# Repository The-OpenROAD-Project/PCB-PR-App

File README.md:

# PCB-PR-App

Top-level app for PCB P&R flow

### Prerequisites

- GCC >=4.8
- G++ >= 4.8
```
export CXX=g++
```
- SWIG >= 2.0
```
sudo apt-get update
sudo apt-get install swig
```
- Boost >= 1.6
```
sudo apt-get update
sudo apt-get install libboost-all-dev
```
- CMake >= 3.1
```
sudo apt-get update
sudo apt-get install cmake
```
- Current support for kicad_pcb format derived from KiCad v5.1.2

### Installing

Clone
```
git clone --recurse-submodules https://github.com/The-OpenROAD-Project/PCB-PR-App.git
```

Run the build script:
```
cd PCB-PR-App
source build.sh
```

The layout app is now available:
```
python3 run_layout.py --help
```

Have fun!

## Running the tests

## Current issues

- Tested on CentOS 6
- Tested on Ubuntu 18.04 (Ubuntu 16.04 doesn't come with Python 3)
- Linking shared object files after swig compilation currently fails on OSX. Docker is a good workaround on OSX.

## License
  * BSD-3-clause License [[Link]](LICENSE)

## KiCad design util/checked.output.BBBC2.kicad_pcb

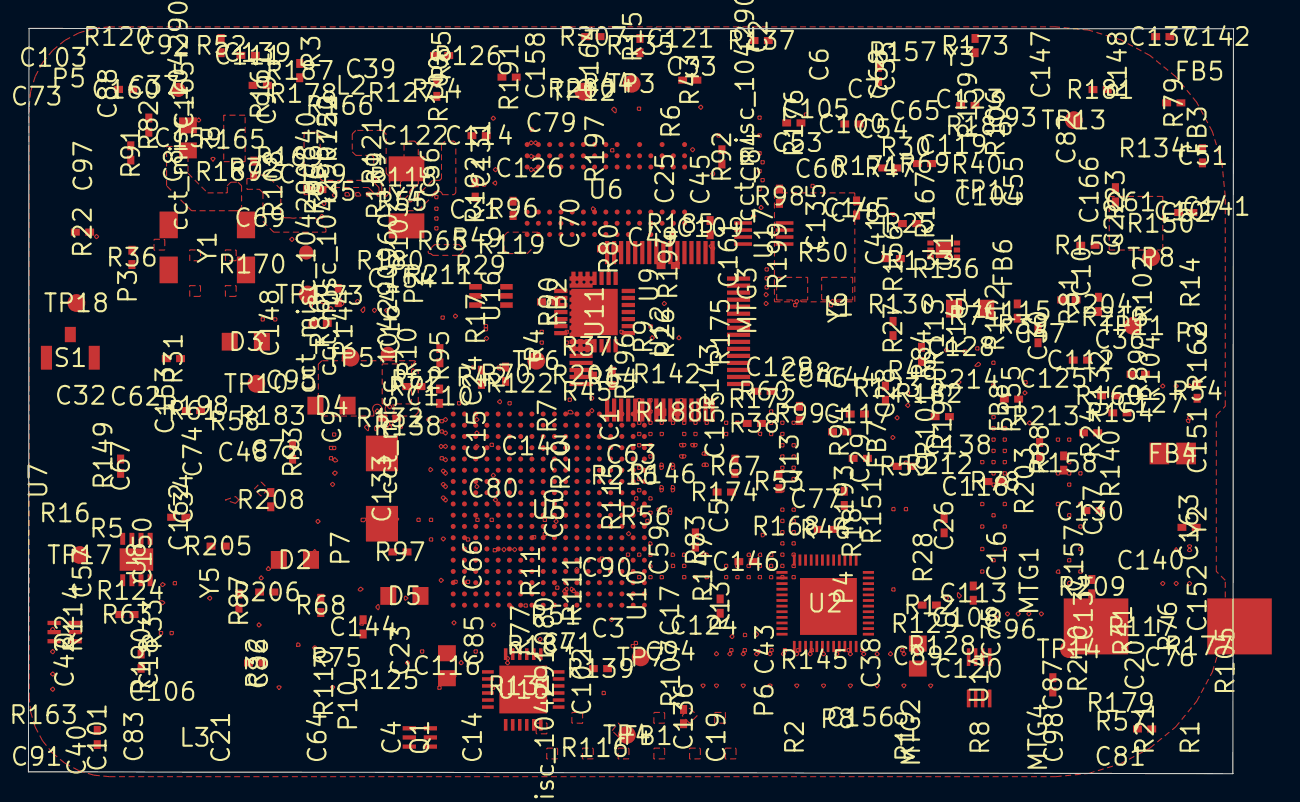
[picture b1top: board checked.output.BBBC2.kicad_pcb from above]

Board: 4 copper layers, 85.7 x 53.0 mm, 452 parts (0 on the bottom side), 309 nets, no tracks yet.

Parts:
C1: C1
C2: C2
C3: C3
C4: C4
C5: C5
C6: C6
C7: C7
C8: C8
C9: C9
C10: C10
C14: C14
C15: C15
C16: C16
C17: C17
C18: C18
C19: C19
C20: C20
C21: C21
C22: C22
C23: C23
C24: C24
C25: C25
C26: C26
C27: C27
C28: C28
C29: C29
C30: C30
C31: C31
C32: C32
C33: C33
C34: C34
C35: C35
C36: C36
C37: C37
C38: C38
C39: C39
C40: C40
C41: C41
C42: C42
C43: C43
C44: C44
C45: C45
C46: C46
C47: C47
C48: C48
C49: C49
C50: C50
C51: C51
C52: C52
C53: C53
C54: C54
C55: C55
C56: C56
C57: C57
C58: C58
C59: C59
C60: C60
C61: C61
C62: C62
C63: C63
C64: C64
C65: C65
C66: C66
C67: C67
C68: C68
C69: C69
C70: C70
C71: C71
C72: C72
C73: C73
C74: C74
C75: C75
C76: C76
C77: C77
C78: C78
C79: C79
C80: C80
C81: C81
C82: C82
C83: C83
C84: C84
C85: C85
C86: C86
C87: C87
C88: C88
C89: C89
C90: C90
C91: C91
C92: C92
C93: C93
C94: C94
C95: C95
C96: C96
C97: C97
C98: C98
C99: C99
C100: C100
C101: C101
C102: C102
C103: C103
C104: C104
C105: C105
C106: C106
C107: C107
C108: C108
C109: C109
C110: C110
C111: C111
C112: C112
C113: C113
C114: C114
C115: C115
C116: C116
C117: C117
C118: C118
C119: C119
C120: C120
C121: C121
C122: C122
C123: C123
C124: C124
C125: C125
C126: C126
C127: C127
C128: C128
C129: C129
C130: C130
C131: C131
C132: C132
C133: C133
C134: C134
C135: C135
C136: C136
C137: C137
C138: C138
C139: C139
C140: C140
C141: C141
C142: C142
C143: C143
C144: C144
C145: C145
C146: C146
C147: C147
C148: C148
C149: C149
C150: C150
C151: C151
C152: C152
C153: C153
C154: C154
C155: C155
C156: C156
C157: C157
C158: C158
C159: C159
C160: C160
C161: C161
C162: C162
C163: C163
C164: C164
C165: C165
C166: C166
D1: D1
D2: D2
D3: D3
D4: D4
D5: D5
FB1: FB1
FB2: FB2
FB3: FB3
FB4: FB4
FB5: FB5
FB6: FB6
FB7: FB7
FB8: FB8
L1: L1
L2: L2
L3: L3
MTG1: MTG1
MTG2: MTG2
MTG3: MTG3
MTG4: MTG4
P2: P2
P3: P3
P4: P4
P5: P5
P6: P6
P7: P7
P8: P8
P9: P9
P10: P10
Q1: Q1
Q2: Q2
R1: R1
R2: R2
R3: R3
R4: R4
R5: R5
R6: R6
R7: R7
R8: R8
R9: R9
R10: R10
R11: R11
R12: R12
R13: R13
R14: R14
R15: R15
R16: R16
R17: R17
R18: R18
R19: R19
R20: R20
R21: R21
R22: R22
R23: R23
R24: R24
R25: R25
R26: R26
R27: R27
R28: R28
R29: R29
R30: R30
R31: R31
R32: R32
R33: R33
R34: R34
R35: R35
R36: R36
R37: R37
R38: R38
R39: R39
R40: R40
R41: R41
R42: R42
R43: R43
R44: R44
R45: R45
R46: R46
R47: R47
R48: R48
R49: R49
R50: R50
R51: R51
R52: R52
R53: R53
R54: R54
R55: R55
R56: R56
R57: R57
R58: R58
R59: R59
R60: R60
R61: R61
R62: R62
R63: R63
R64: R64
R65: R65
R66: R66
R67: R67
R68: R68
R69: R69
R70: R70
R71: R71
R72: R72
R73: R73
R74: R74
R75: R75
R76: R76
R77: R77
R78: R78
R79: R79
R80: R80
R81: R81
R82: R82
R83: R83
R84: R84
R85: R85
R86: R86
R87: R87
R88: R88
R89: R89
R90: R90
R91: R91
R92: R92
R93: R93
R94: R94
R95: R95
R96: R96
R97: R97
R98: R98
R99: R99
R100: R100
R101: R101
R102: R102
R103: R103
R104: R104
R105: R105
R106: R106
R107: R107
R108: R108
R109: R109
R110: R110
R111: R111
R112: R112
R113: R113
R114: R114
R115: R115
R116: R116
R117: R117
R118: R118
R119: R119
R120: R120
R121: R121
R122: R122
R123: R123
R124: R124
R125: R125
R126: R126
R127: R127
R128: R128
R129: R129
R130: R130
R131: R131
R132: R132
R133: R133
R134: R134
R135: R135
R136: R136
R137: R137
R138: R138
R139: R139
R140: R140
R141: R141
R142: R142
R143: R143
R144: R144
R145: R145
R146: R146
R147: R147
R148: R148
R149: R149
R150: R150
R151: R151
R152: R152
R153: R153
R154: R154
R155: R155
R156: R156
R157: R157
R158: R158
R159: R159
R160: R160
R161: R161
R162: R162
R163: R163
R164: R164
R165: R165
R166: R166
R167: R167
R168: R168
R169: R169
R170: R170
R171: R171
R172: R172
R173: R173
R174: R174
R175: R175
R176: R176
R177: R177
R178: R178
R179: R179
R180: R180
R181: R181
R182: R182
R183: R183
R184: R184
R185: R185
R186: R186
R187: R187
R188: R188
R189: R189
R190: R190
R191: R191
R192: R192
R193: R193
R194: R194
R195: R195
R196: R196
R197: R197
R198: R198
R199: R199
R200: R200
R201: R201
R203: R203
R204: R204
R205: R205
R206: R206
R207: R207
R208: R208
R209: R209
R210: R210
R211: R211
R212: R212
R213: R213
R214: R214
R215: R215
R216: R216
S1: S1
TP1: TP1
TP3: TP3
TP4: TP4
TP5: TP5
TP6: TP6
TP7: TP7
TP8: TP8
TP10: TP10
TP11: TP11
TP12: TP12
TP13: TP13
TP14: TP14
TP15: TP15
TP17: TP17
TP18: TP18
U1: U1
U2: U2
U5: U5
U6: U6
U7: U7
U8: U8
U9: U9
U10: U10
U11: U11
U12: U12
U13: U13
U14: U14
U15: U15
U16: U16
U17: U17
Y1: Y1
Y2: Y2
Y3: Y3
Y4: Y4
Y5: Y5
Y6: Y6
cct_misc_104290480: cct_misc_104290480
cct_misc_104290600: cct_misc_104290600
cct_misc_104290720: cct_misc_104290720
cct_misc_104290840: cct_misc_104290840
cct_misc_104290960: cct_misc_104290960
cct_misc_104291080: cct_misc_104291080

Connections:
3V3EXP_FB: C166.1, R150.1, R189.1, U8.3
AGND: R15.1, U2.41
AIN7: R8.1, R9.2, U5.C9
BAT: C3.2, U2.4, U2.5
BL_OUT: C7.1, U2.38
CAP_VBB_MPU: C85.1, U5.C10
CAP_VDD_SRAM_CORE: C83.1, U5.D9
CAP_VDD_SRAM_MPU: C84.1, U5.D11
CD/EMU4: R185.1, R197.2, U5.C15
CLKOUT2: R184.2, U5.D14
COL/CRS_DV/MODE2: R207.2, U15.15
CRFILT: C146.1, U11.9
CRS_DV/MODE2: R122.1, R127.1, R139.2, U15.14
DC_IN: C1.1, U1.4, U1.5, U2.10
DDR_A0: R29.1, U6.M8
DDR_A1: R25.1, U6.M3
DDR_A2: R30.1, U6.M7
DDR_A3: R26.1, U6.N2
DDR_A4: R31.1, U6.N8
DDR_A5: R32.1, U6.N3
DDR_A6: R33.1, U6.N7
DDR_A7: R34.1, U6.P2
DDR_A8: R35.1, U6.P8
DDR_A9: R36.1, U6.P3
DDR_A10: R37.1, U6.M2
DDR_A11: R38.1, U6.P7
DDR_A12: R39.1, U6.R2
DDR_A13: R40.1, R120.1
DDR_A13R: R120.2, U6.R8
DDR_BA0: R41.1, U6.L2
DDR_BA1: R42.1, U6.L3
DDR_BA2: R43.1, U6.L1
DDR_CASN: R64.1, U6.L7
DDR_CKE: R62.1, U6.K2
DDR_CLK: R60.1, U6.J8
DDR_CLKN: R61.1, U6.K8
DDR_CSN: R63.1, U6.L8
DDR_D0: R44.1, U6.G8
DDR_D1: R45.1, U6.G2
DDR_D2: R46.1, U6.H7
DDR_D3: R47.1, U6.H3
DDR_D4: R48.1, U6.H1
DDR_D5: R49.1, U6.H9
DDR_D6: R50.1, U6.F1
DDR_D7: R51.1, U6.F9
DDR_D8: R52.1, U6.C8
DDR_D9: R53.1, U6.C2
DDR_D10: R54.1, U6.D7
DDR_D11: R55.1, U6.D3
DDR_D12: R56.1, U6.D1
DDR_D13: R57.1, U6.D9
DDR_D14: R58.1, U6.B1
DDR_D15: R59.1, U6.B9
DDR_DQM0: R67.1, U6.F3
DDR_DQM1: R70.1, U6.B3
DDR_DQS0: R68.1, U6.F7
DDR_DQS1: R71.1, U6.B7
DDR_DQSN0: R69.1, U6.E8
DDR_DQSN1: R72.1, U6.A8
DDR_ODT: R73.1, U6.K9
DDR_RASN: R65.1, U6.K7
DDR_RESETN: TP3.1, U5.G2
DDR_VREF: C118.1, R74.2, R75.1, U5.J4, U6.J2
DDR_VTP: R76.1, U5.J3
DDR_WEN: R66.1, U6.K3
DGND: C1.2, C2.2, C3.1, C4.1, C5.1, C6.2, C7.2, C8.1, C9.1, C10.1, C14.1, C15.1, C16.2, C17.1, C18.1, C19.1, C20.2, C21.2, C22.2, C25.2, C31.1, C32.1, C33.2, C34.2, C35.2, C36.2, C37.2, C38.2, C39.2, C40.2, C41.2, C42.2, C43.1, C44.1, C45.2, C46.2, C47.2, C48.2, C49.2, C50.1, C51.2, C52.1, C53.2, C54.2, C55.2, C56.2, C57.2, C58.1, C59.1, C60.2, C61.2, C62.1, C63.1, C64.1, C65.1, C66.1, C67.1, C68.1, C69.2, C70.1, C71.1, C72.2, C73.2, C74.2, C75.2, C76.2, C77.2, C78.2, C79.2, C80.2, C81.2, C82.2, C83.2, C84.2, C85.2, C86.2, C88.2, C89.1, C90.2, C91.2, C92.2, C93.2, C94.2, C95.2, C96.2, C97.2, C98.2, C100.2, C101.2, C102.2, C103.2, C104.2, C105.2, C106.2, C107.2, C108.2, C109.2, C110.2, C111.2, C112.2, C113.2, C114.2, C115.2, C116.2, C117.2, C118.2, C119.2, C120.2, C121.2, C122.2, C123.2, C124.2, C125.2, C126.2, C127.2, C128.2, C129.2, C130.2, C131.2, C132.2, C133.2, C134.2, C135.1, C136.2, C137.1, C138.2, C139.2, C140.2, C141.2, C142.2, C143.2, C144.1, C145.2, C146.2, C147.2, C148.2, C149.1, C150.2, C151.2, C152.2, C153.1, C154.2, C155.1, C156.2, C157.1, C158.2, C159.2, C160.2, C161.2, C162.1, C163.1, C164.1, C165.1, D1.1, FB3.2, P3.5, P4.6, P4.9, P7.8, P7.10, P7.12, P7.16, P7.20, Q1.1, Q1.4, Q2.1, Q2.4, R1.1, R5.2, R9.1, R15.2, R16.1, R18.2, R20.2, R75.2, R76.2, R79.1, R100.2, R101.2, R102.2, R103.2, R104.2, R105.2, R106.2, R107.2, R108.2, R109.2, R110.2, R111.2, R112.2, R113.2, R114.2, R115.2, R116.2, R117.2, R118.2, R119.2, R125.2, R127.2, R128.1, R138.1, R145.2, R146.2, R147.2, R151.2, R157.2, R158.2, R159.2, R161.1, R167.1, R177.2, R186.2, R189.2, R198.2, R212.2, R214.2, R216.2, S1.1, U1.2, U1.6, U2.30, U2.49, U5.A1, U5.A18, U5.F8, U5.G8, U5.G9, U5.G11, U5.G12, U5.H6, U5.H7, U5.H8, U5.H9, U5.H10, U5.H12, U5.J6, U5.J7, U5.J8, U5.J9, U5.J10, U5.J11, U5.K7, U5.K9, U5.K10, U5.K11, U5.L10, U5.L11, U5.L12, U5.L13, U5.M6, U5.M7, U5.M8, U5.M9, U5.M10, U5.M12, U5.M14, U5.N7, U5.N10, U5.N11, U5.N14, U5.V1, U5.V18, U6.A3, U6.A7, U6.B2, U6.B8, U6.D2, U6.D8, U6.E3, U6.E7, U6.F2, U6.F8, U6.H2, U6.H8, U6.J3, U6.J7, U6.N1, U6.P9, U7.1, U8.4, U8.9, U9.9, U10.4, U11.6, U11.29, U12.1, U12.5, U12.10, U12.11, U12.13, U12.15, U12.25, U12.32, U12.35, U12.47, U12.51, U13.2, U14.4, U15.33, U16.2, U17.4
EMU2R: P7.17, R183.2
EMU3R: P7.18, R184.1
EMU4R: P7.19, R185.2
EMU_RSTN: C156.1, P7.15, R182.2
ENZ_KALDO_1P8V: R79.2, U5.B4
FT_DM: U11.28, U12.7
FT_DP: U11.1, U12.8
FT_REF: R167.2, U12.6
FT_RESETN: R175.2, U12.14
FT_SRESET: R162.2, R172.2, R182.1, U14.5
FT_SRESETB: R163.1, U16.6
FT_SRESETN: U14.3, U16.1
FT_VBUS: R181.2, U11.7, U12.59, U14.6
F_ADBUS0: R164.1, U12.16
F_ADBUS1: R165.1, U12.17
F_ADBUS2: R166.1, U12.18
F_ADBUS3: R168.1, U12.19
F_ADBUS4: R169.1, U12.21
F_ADBUS5: R172.1, U12.26
F_ADBUS6: R170.1, U12.23
F_ADBUS7: R171.1, U12.30
F_EECS: R173.2, U12.63, U13.5
F_EEDATA: R188.2, U12.61, U13.3
F_EEDOUT: R187.2, R188.1, U13.1
F_EESK: R174.2, U12.62, U13.4
GNDA_ADC: C28.2, C29.2, C30.2, C87.2, FB3.1, U5.A9, U5.E8
GND_EARTH: P3.6, P3.7, P3.8, P3.9, P4.11, P4.12, P4.13, P4.14, P4.15, P4.16, R138.2, S1.3
GND_OSC0: C26.2, C27.2, C99.2, U5.V11
GND_OSC1: C23.1, C24.1, U5.A5
GPIO2_6: R80.2, R100.1, U5.R1
GPIO2_7: R81.2, R101.1, U5.R2
GPIO2_8: R82.2, R102.1, U5.R3
GPIO2_9: R83.2, R103.1, U5.R4
GPIO2_10: R84.2, R104.1, U5.T1
GPIO2_11: R85.2, R105.1, U5.T2
GPIO2_13: R87.2, R107.1, U5.T4
GPIO_12: R86.2, R106.1, U5.T3
HS_IND: TP8.1, U11.16
HUB_BIAS: R157.1, U11.26
I2C0_SCL: R7.2, U2.28, U5.C16
I2C0_SDA: R4.2, U2.27, U5.C17
JTAG_EMU0: P7.13, R170.2, R176.2, U5.C14
JTAG_EMU1: P7.14, R171.2, R179.2, U5.B14
JTAG_TCK: R164.2, R178.1, R180.1, U5.A12
JTAG_TDI: P7.3, R165.2, U5.B11
JTAG_TDO: P7.7, R166.2, U5.A11
JTAG_TMS: P7.1, R168.2, U5.C11
JTAG_TRSTN: P7.2, R169.2, R186.1, U5.B10
LDO3: R19.1, U2.40
LDO4: R121.1, U2.43
LDO_PGOOD: R141.2, U2.46
LEDAA: D2.2, R96.2, TP10.1
LEDAC: D2.1, Q1.6
LEDBA: D3.2, R97.2, TP11.1
LEDBC: D3.1, Q1.3
LEDCA: D4.2, R98.2, TP12.1
LEDCC: D4.1, Q2.6
LEDDA: D5.2, R99.2, TP13.1
LEDDC: D5.1, Q2.3
MDIO_DATA: R131.2, U5.M17
MMC0_CLKO: P4.5, R192.2, U5.G17
MMC0_CMD: P4.3, R191.2, U5.G18
MMC0_DAT0: P4.7, R193.2, U5.G16
MMC0_DAT1: P4.8, R194.2, U5.G15
MMC0_DAT2: P4.1, R190.2, U5.F18
MMC0_DAT3: P4.2, R195.2, U5.F17
N21069846: R199.2, R200.2, U15.5
NINT/RXCLK/PHYAD1: R215.1, R216.1
NON_REM1: R154.2, R158.1, U11.13
NON_REM2: R155.2, R159.1, TP7.1, U11.19
OSC0_IN: C26.1, R21.1, U5.V10, Y2.3, Y3.3
OSC0_OUT: R24.2, U5.U11
OSC0_OUT1: C27.1, R21.2, R24.1, Y2.1, Y3.1
OSC1_IN: C23.2, U5.A6, Y1.1
OSC1_OUT: R22.2, U5.A4
OSC1_OUT1: C24.2, R22.1, Y1.2
PDDR_A0: R29.2, U5.F3
PDDR_A1: R25.2, U5.H1
PDDR_A2: R30.2, U5.E4
PDDR_A3: R26.2, U5.C3
PDDR_A4: R31.2, U5.C2
PDDR_A5: R32.2, U5.B1
PDDR_A6: R33.2, U5.D5
PDDR_A7: R34.2, U5.E2
PDDR_A8: R35.2, U5.D4
PDDR_A9: R36.2, U5.C1
PDDR_A10: R37.2, U5.F4
PDDR_A11: R38.2, U5.F2
PDDR_A12: R39.2, U5.E3
PDDR_A13: R40.2, U5.H3
PDDR_BA0: R41.2, U5.C4
PDDR_BA1: R42.2, U5.E1
PDDR_BA2: R43.2, U5.B3
PDDR_CASN: R64.2, U5.F1
PDDR_CKE: R62.2, U5.G3
PDDR_CLK: R60.2, U5.D2
PDDR_CLKN: R61.2, U5.D1
PDDR_CSN: R63.2, U5.H2
PDDR_D0: R44.2, U5.M3
PDDR_D1: R45.2, U5.M4
PDDR_D2: R46.2, U5.N1
PDDR_D3: R47.2, U5.N2
PDDR_D4: R48.2, U5.N3
PDDR_D5: R49.2, U5.N4
PDDR_D6: R50.2, U5.P3
PDDR_D7: R51.2, U5.P4
PDDR_D8: R52.2, U5.J1
PDDR_D9: R53.2, U5.K1
PDDR_D10: R54.2, U5.K2
PDDR_D11: R55.2, U5.K3
PDDR_D12: R56.2, U5.K4
PDDR_D13: R57.2, U5.L3
PDDR_D14: R58.2, U5.L4
PDDR_D15: R59.2, U5.M1
PDDR_DQM0: R67.2, U5.M2
PDDR_DQM1: R70.2, U5.J2
PDDR_DQS0: R68.2, U5.P1
PDDR_DQS1: R71.2, U5.L1
PDDR_DQSN0: R69.2, U5.P2
PDDR_DQSN1: R72.2, U5.L2
PDDR_ODT: R73.2, U5.G1
PDDR_RASN: R65.2, U5.G4
PDDR_WEN: R66.2, U5.B2
PHYX: C131.1, R144.2, Y4.2
PHY_VDDCR: C124.1, C125.1, U15.6
PHY_XTAL1: C132.1, R140.2, R199.1, Y4.1
PHY_XTAL2: R140.1, R144.1, U15.4
PLLFILT: C145.1, U11.25
PMIC_INT: R10.2, R28.2, U5.B18
PMIC_INT_PU: R28.1, U14.7
PMIC_INT_SRC: R10.1, R203.2, U2.45, U14.1, U14.2
PMIC_PGOOD: C25.1, R20.1, U2.26, U5.B15
PMIC_POWR_EN: U2.9, U5.C6
PWR_LED: R6.1, U2.1
PWR_LEDR: D1.2, R6.2, TP14.1
P_BYPASS: C5.2, U2.47
P_INT_LDO: C4.2, U2.48
P_MUXIN: R1.2, R2.1, U2.14
P_MUXOUT: R8.2, U2.16
P_WAKEUP: R11.1, U2.13
REFCLKO: R136.2, R209.2, U15.7
RESETN: C136.1, R156.2, U11.17
RMII1_COL: R207.1, U5.H16
RMII1_CRS_DV: R139.1, U5.H17
RMII1_REFCLK: R200.1, R201.2, R209.1
RMII1_RXCLK: R136.1, U5.L18
RMII1_RXD0: R135.1, U5.M16
RMII1_RXD1: R132.1, U5.L15
RMII1_RXD2: R153.1, U5.L16
RMII1_RXD3: R205.1, U5.L17
RMII1_RXDV: R208.1, U5.J17
RMII1_RXERR: R137.1, U5.J15
RMII1_TXCLK: R206.1, U5.K18
RMII1_TXD0: U5.K17, U15.22
RMII1_TXD1: U5.K16, U15.23
RMII1_TXEN: U5.J16, U15.21
RSVD3: R161.2, U11.15
RTCK: P7.9, R178.2
RTC_PORZ: R18.1, R141.1, R143.2, U5.B5
RXD0/MODE0: R124.1, R135.2, R198.1, U15.11
RXD1/MODE1: R5.1, R123.1, R132.2, U15.10
RXD2/RMIISEL: R153.2, R211.1, R212.1
RXD3/PHYAD2: R205.2, R213.1, R214.1
RXDV: R208.2, U15.26
RXER/PHYAD0: R125.1, R126.2, R137.2, U15.13
RXN: C127.1, R130.1, U15.30
RXP: C126.1, R129.1, U15.31
SD_CD: P4.10, R196.1, R197.1
SYS_5V: C133.1, FB4.2, R3.2, R152.1, U2.7, U2.8
SYS_RESETN: R23.2, R27.1, U5.A10, U15.19
SYS_VOLT: C6.1, C8.2, C9.2, C10.2, C17.2, C18.2, C19.2, R2.2, R3.1, U2.2, U2.21, U2.22, U2.32, U2.39, U2.42, U8.8
SYS_WARMRESETN: C101.1, R27.2, R163.2, S1.2
TCK: P7.11, R180.2
TCT_RCT: C130.1, R142.1
TDIS: P7.4, R177.1
TESTOUT: TP6.1, U5.A3
TXCLK: R206.2, U15.20
TXN: C129.1, R134.1, U15.28
TXP: C128.1, R133.1, U15.29
U5_H18: R201.1, U5.H18
UART0_CTS: U5.E17, U12.40
UART0_RTS: U5.E18, U12.41
UART0_RX: U5.E16, U12.39
UART0_TX: U5.E15, U12.38
UART3_CTSN: R90.2, R110.1, U5.U3
UART3_RTSN: R91.2, R111.1, U5.U4
UART4_CTSN: R92.2, R112.1, U5.V2
UART4_RTSN: R93.2, R113.1, U5.V3
UART5_CTSN: R94.2, R114.1, U5.V4
UART5_RTSN: R95.2, R115.1, U5.T5
UART5_RXD: R89.2, R109.1, U5.U2
UART5_TXD: R88.2, R108.1, U5.U1
USB0_DM: U5.N18, U11.2
USB0_DP: U5.N17, U11.3
USB0_ID: TP4.1, U5.P16
USB0_VBUS: R152.2, U5.P15, U16.4
USB0_VBUS_PWR: U11.11, U16.3
USB1_DM: U5.R18, U10.2
USB1_DP: U5.R17, U10.1
USB1_DRVVBUS: R147.1, U5.F15
USB1_ID: R146.1, U5.P17
USB1_OC: R148.2, U5.T16
USB1_VBUS: C134.1, U5.T18, U10.6
USBDM_DN: P3.2, U11.21
USBDP_UP: P3.3, U11.22
USB_DC: C2.1, P3.1, R149.1, U2.12
USR0: Q1.2, R116.1, U5.V15
USR1: Q1.5, R117.1, U5.U15
USR2: Q2.2, R118.1, U5.T15
USR3: Q2.5, R119.1, U5.V16
VBUS_DET: R149.2, R151.1, U11.18
VDCDC1: R12.1, U2.19
VDCDC2: R204.1, U2.24
VDCDC3: R13.1, U2.29
VDDS_DDR: C89.2, C90.1, C91.1, C92.1, C93.1, C94.1, C95.1, C96.1, C103.1, C104.1, C105.1, C106.1, C107.1, C108.1, C109.1, C110.1, C111.1, C112.1, C113.1, C114.1, C115.1, C116.1, C117.1, R14.2, R74.1, TP18.1, U5.E5, U5.F5, U5.G5, U5.H5, U5.J5, U5.K5, U5.L5, U6.A1, U6.A9, U6.C1, U6.C3, U6.C7, U6.C9, U6.E1, U6.E9, U6.G1, U6.G3, U6.G7, U6.G9, U6.J1, U6.J9, U6.M9, U6.R1
VDD_1V8: C16.1, C72.1, C74.1, C75.1, C76.1, C77.1, C78.1, C79.1, C80.1, C82.1, C86.1, FB1.1, FB2.2, R12.2, R14.1, TP15.1, U5.D10, U5.E6, U5.E7, U5.E9, U5.E14, U5.F9, U5.K13, U5.N6, U5.N16, U5.P9, U5.P14, U5.R16
VDD_1V8FT: C152.1, C162.2, C163.2, C164.2, U12.12, U12.37, U12.49, U12.64
VDD_3V3A: C42.1, C43.2, C51.1, C52.2, C56.1, C57.1, C58.2, C59.2, C60.1, C61.1, C62.2, C63.2, C64.2, C65.2, C66.2, C67.2, C68.2, C69.1, C70.2, C71.2, C81.1, C159.1, C160.1, C165.2, P4.4, R4.1, R7.1, R19.2, R23.1, R80.1, R81.1, R82.1, R83.1, R84.1, R85.1, R86.1, R87.1, R88.1, R89.1, R90.1, R91.1, R92.1, R93.1, R94.1, R95.1, R190.1, R191.1, R192.1, R193.1, R194.1, R195.1, U2.18, U5.E10, U5.E11, U5.E12, U5.E13, U5.F14, U5.G14, U5.H14, U5.J14, U5.K14, U5.L14, U5.N5, U5.N15, U5.P5, U5.P6, U5.P7, U5.P8, U5.P10, U5.P11, U5.P12, U5.P13, U5.R15, U8.5
VDD_3V3B: C102.1, C122.1, C123.1, C135.2, C138.1, C139.1, C140.1, C141.1, C142.1, C143.1, C147.1, C148.1, C149.2, C150.1, C151.1, C154.1, C157.2, FB5.1, FB6.1, FB7.1, FB8.1, P7.5, R121.2, R122.2, R123.2, R124.2, R126.1, R131.1, R148.1, R154.1, R155.1, R156.1, R162.1, R173.1, R174.1, R175.1, R176.1, R179.1, R181.1, R187.1, R196.2, R203.1, R210.1, R211.2, R213.2, R215.2, U11.4, U11.10, U11.14, U11.20, U11.27, U12.20, U12.28, U12.31, U12.42, U12.56, U13.6, U14.8, U15.12, U16.5
VDD_3V3EXP: C166.2, R150.2, U8.1
VDD_5V: U1.1, U1.7
VDD_ADC: C87.1, FB2.1, R78.1, U5.D8
VDD_CORE: C14.2, C31.2, C32.2, C33.1, C34.1, C35.1, C36.1, C37.1, C38.1, C39.1, C40.1, C41.1, C48.1, C49.1, C50.2, C53.1, C54.1, C55.1, R13.2, TP17.1, U5.F6, U5.F7, U5.G6, U5.G7, U5.G10, U5.H11, U5.J12, U5.K6, U5.K8, U5.K12, U5.L6, U5.L7, U5.L8, U5.L9, U5.M5, U5.M11, U5.M13, U5.N8, U5.N9, U5.N12, U5.N13
VDD_FTREGIN: FB8.2, U12.50
VDD_FTVPHY: C158.1, FB7.2, U12.4
VDD_FTVPLL: C161.1, FB6.2, U12.9
VDD_LED: C100.1, FB4.1, R96.1, R97.1, R98.1, R99.1
VDD_MPU: C15.2, C44.2, C45.1, C46.1, C47.1, R204.2, U5.F10, U5.F11, U5.F12, U5.F13, U5.G13, U5.H13, U5.J13
VDD_MPUON: TP5.1, U5.A2
VDD_PHYA: C119.1, C120.1, C121.1, FB5.2, R129.2, R130.2, R133.2, R134.2, R142.2, U15.27
VDD_PLL: C73.1, C88.1, C99.1, FB1.2, U5.H15, U5.R10, U5.R11
VDD_RTC: C97.1, U5.D6
VREFP_ADC: C28.1, C29.1, C30.1, R78.2, U5.B9
VRTC: C20.1, C21.1, C98.1, R77.1, U2.3, U5.D7, U17.1, U17.2, U17.8
VRTC_DET: R17.1, U17.7
VRTC_DETB: C22.1, R17.2, U17.5, U17.6
VRTC_DET_OUT: R143.1, U17.3
WAKEUP: R11.2, R77.2, U5.C5
XDMA_EVENT_INTR0: R183.1, U5.A15
XTALIN: C137.2, R160.1, U11.24, Y5.3
XTALOUT: C144.2, R160.2, U11.23, Y5.1
XTIN: C153.2, U12.2, Y6.3
XTOUT: C155.2, U12.3, Y6.1

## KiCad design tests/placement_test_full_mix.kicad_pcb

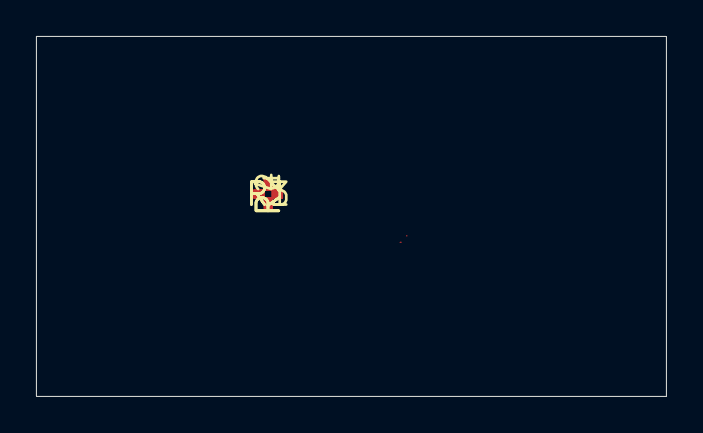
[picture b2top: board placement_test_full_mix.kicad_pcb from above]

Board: 4 copper layers, 35.0 x 20.0 mm, 8 parts (0 on the bottom side), 7 nets.

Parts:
R1: R1
R2: R2
R3: R3
R4: R4
R5: R5
R6: R6
R7: R7
R8: R8

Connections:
N2: R1.1, R2.2
N3: R2.1, R3.2
N4: R3.1, R4.2
N5: R4.1, R5.2
N6: R5.1, R6.2
N7: R6.1, R7.2
N8: R7.1, R8.2

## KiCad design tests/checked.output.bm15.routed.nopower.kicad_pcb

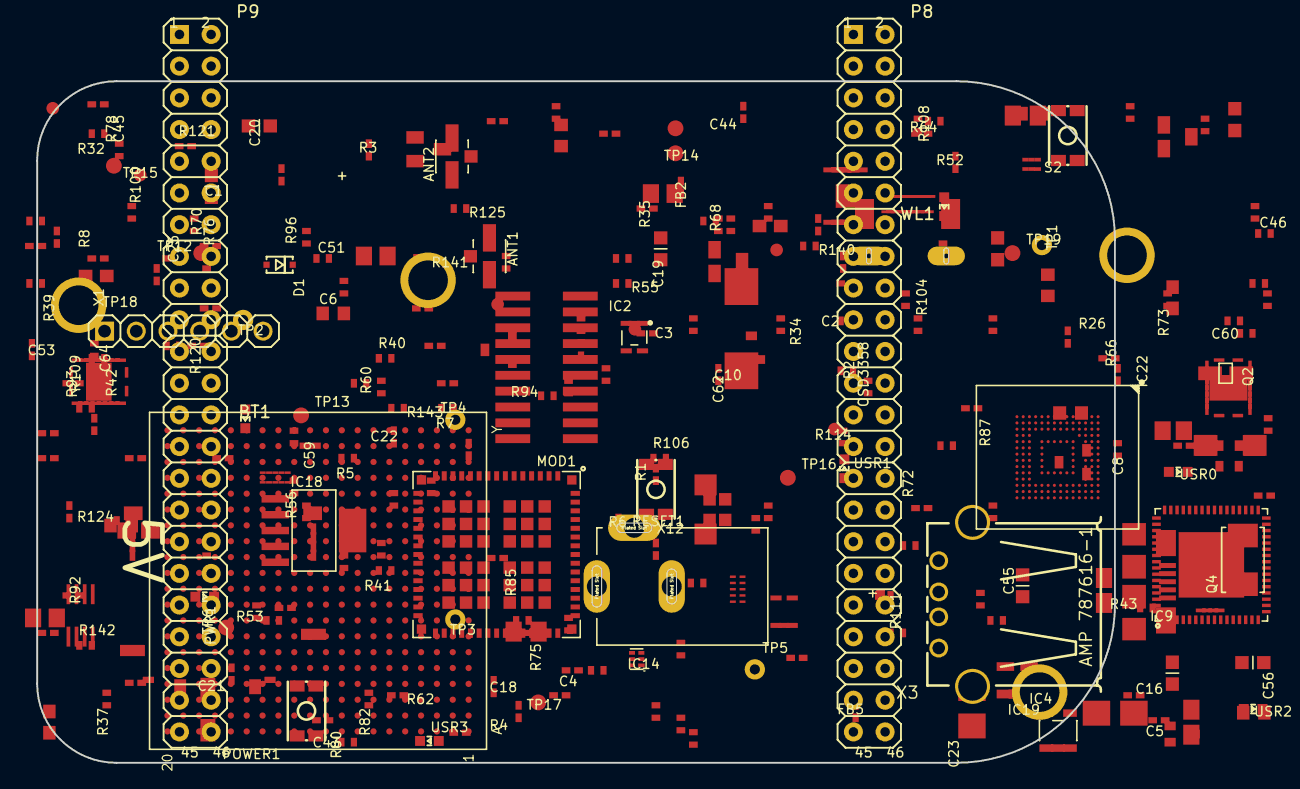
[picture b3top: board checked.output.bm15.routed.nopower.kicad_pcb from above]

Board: 6 copper layers, 86.4 x 54.6 mm, 275 parts (0 on the bottom side), 248 nets, no tracks yet.

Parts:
ANT1, ANT2: U.FL-R-SMT-1(10); U.FL-R-SMT-1
BT1: LTST-C191TBKT; 0603-LED
C1: 10uF,10V; C0603K
C2, C13, C15, C17, C18, C21, C22, C24, C25, C43, C44, C45, C47, C48, C49, C50, C51, C52, C53, C58, C59, C63, C69: .1uF, 6.3V; C0402K
C3, C4, C5, C6: 18pF, 50V; C0402K
C7: 4.7uF, 6.3V; C0805K
C8, C10: 1uF; C0402K
C9, C12, C14: 2.2uF, 6.3V; C0805K
C11, C23: 47uF DNP; CT3528
C16, C54, C55, C56, C57: 2.2uF, 6.3V; C0603K
C19, C20, C61: 10uF, 6.3V; C0603K
C27, C28, C29, C30, C31, C32, C33, C34, C35, C36, C37, C38, C39, C40, C41, C42: 47pF, 6.3V; C0402K
C46, C60: 10pF; C0402K
C62: 220uF 6.3V; D_7343-31W
C64: 1uF, 6.3V; C0402K
D1: RB751V40,115; SOD323(NXP)REFLOW
D2: STPS140A DNP; DIODE_SMA
D3, D4: STPS140A; DIODE_SMA
D8: BAT54C; SOT23
F1: 1206L025YR; SM-1206
FB1: 220 Ohm 800mA; 0805-RESISTOR
FB2: 2.5k Ohm (BLM18BD252SN1D); 0805-RESISTOR
FB3: 150 Ohm 800mA; 0805-RESISTOR
FB4: 0.1 Ohm, 0805; 0805-RESISTOR
FB5, FB6, FB7: 1k BLM15AG102SN1D; R0402
FUD1, FUD2, FUD3, FUD4, FUD5, FUD6: FIDUCIAL; FIDUCIAL_40MIL
IC1: OSD3358
IC2: SN74LVC1G07DCK; SC70(TI-DCK)
IC3: SN74LVC1G06DCK; SC70(TI-DCK)
IC4: 24LC32AT-I/OT; SOT23-5(MICROCHIP)
IC5: TLVH431 (SOT-23-3); DBZ_R-PDSO-G3
IC6: DNP TLVH431 (SOT-23-3); DBZ_R-PDSO-G3
IC7, IC8: IP4283CZ10-TBR; SOT1176-1(NXP)
IC9: TDA19988BHN/C1,557; SOT804-4(NXP)
IC10, IC11: TXS0108ERGYR; R-PVQFN-N20(TI)
IC12: TPS2051BDGN; MSOP-POWER.PAD-8(TI)
IC13: SN74AUC1G74; SM8-8(TI)
IC14, IC15: TPD4S012DRY; SON-6(TI)-DRY
IC17: SN74LVC2G241DCUR; VSSOP8(TI)
IC18: TL1963ADCQR; SOT-223(DCQ_R-PDSO-G6_TI)
IC19: AP2112K-1.8TRG1 3.3V; SOT23-5
IC22: EMMC04G-S100-B08U; MICRON_EMMC_153
MGT1, MGT2, MGT3, MGT4: MOUNTING_HOLE
MOD1: WL1835MODGBMOCT; MOC-100(TI)
OSC1: ASDMB-24.576MHZ-LC-T; OSCILLATOR-2.5X2.0-BBB
OSC2: NZ2520SB-32.768KHZ-NSA3534C; NZ2520S
P2: JTAG
P8, P9: HEADER-2X23-(INCH)-0.1-TH; TH-2X23
POWER1: MINI_PUSHBUTTON
PWR1: LTST-C191TBKT; 0603-LED
Q2: 32.768kHz; CRYSTAL_3.2X1.5
Q4: 24 MHz; CRYSTAL_5X3.2MM
R1, R2, R3, R4, R5, R6, R7, R12, R13, R16, R18, R19, R20, R23, R24, R25, R28, R30, R31, R32, R33, R40, R119, R121: 10k, 1%; R0402
R8: 1M, 1%; R0402
R10, R11: 150k; R0402
R14, R26, R27, R29, R35, R36, R37, R38, R39, R54, R114, R122: 0, 1%; R0402
R17: .1, 0805; R0805
R21, R22, R43, R52, R53, R55: 4.75k, 1%; R0402
R34: 22; R0402
R41, R42, R115, R118: 1.5k, 1%; R0402
R44: 499; R0402
R45, R49: DNP; R0402
R46: 10k 1%; R0402
R47: 40.2k 1%; R0402
R48: DNP 499; R0402
R50: DNP 10k 1%; R0402
R51: DNP 40.2k 1%; R0402
R56: DNP 1M, 1%; R0402
R57, R58, R61, R63, R65, R67, R69, R71, R73, R75, R76, R78, R80, R82, R85, R87, R123: 100k, 1%; R0402
R60, R62, R64, R66, R68, R70, R72, R140, R141, R142, R143: 33, 5%; R0402
R86, R126, R127, R128, R129, R130, R131, R134, R135, R136: 33, 5%; R0603
R88: 100, 1%; R0402
R89, R90, R92, R96, R100, R104, R124, R125: 1k; R0402
R91: 0 DNP; R0402
R93: 7.15k; R0402
R94: 4.12k; R0402
R95: 1M; R0402
R97, R108, R109: DNP 1k; R0402
R98, R99, R101, R102, R103, R105: 10k; R0402
R106: 1.5k; R0402
R110: 33; R0402
R111: DNP 10k; R0402
R120: 27k, 1%; R0402
RESET1: MINI_PUSHBUTTON
S2: MINI_PUSHBUTTON
T1: MMBT2907; SOT23-BEC
T2: DNP MMBT2907; SOT23-BEC
T3, T4: BSS138W-7-F; SOT-323(DIODES)
TP1, TP2, TP3, TP4, TP5: TESTPAD_W_HOLE_1X1
TP6, TP12, TP13, TP14, TP15, TP16, TP17, TP18, TP19, TP23: PTR1B1,27; B1,27
USR0, USR1, USR2, USR3: LTST-C191TBKT; 0603-LED
WL1: LTST-C191TBKT; 0603-LED
X1: 1X6-(INCH)-0.1-TH; TH-1X6
X2: SCHA5B0200
X3: USB_HOST_W_CHASSIS_GND; USB_HOST_HORIZONTAL_W_CHASSIS_GND
X4: 10118192-0001LF; 10118192-0001LF(MICRO-USB-B-AMPHENOL-FCI)
X5: 10118241-001RLF; HDMI-TYPE-D-10118241
X12: PJ-102B_POWER_CON

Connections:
/5V_IN: C19.1, D8.3, FB1.2, IC18.2, R95.1
/12MHZ: FB6.2, IC9.27
/12M_LOOP: IC13.2, IC13.3
/32.768KHZ: MOD1.36, OSC2.3, R91.2
/AIN0: IC1.B6, P9.39
/AIN1: IC1.C7, P9.40
/AIN2: IC1.B7, P9.37
/AIN3: IC1.A7, P9.38
/AIN4: IC1.C8, P9.33
/AIN5: IC1.B8, P9.36
/AIN6: IC1.A8, P9.35
/BAT_TEMP: IC1.W1, TP4.P$1
/BAT_VOLT: IC1.Y1, TP3.P$1
/BT_EN: IC11.4, MOD1.41, R11.1, T4.G
/BT_EN.SIP: IC1.K17, R135.1
/BT_HCI_CTS: IC11.8, R141.2
/BT_HCI_CTS.SIP: IC1.M17, IC11.15, R108.1
/BT_HCI_RTS: IC11.6, R140.2
/BT_HCI_RTS.SIP: IC1.M18, IC11.13, R109.1
/BT_HCI_RX: IC11.1, R143.2
/BT_HCI_RX.SIP: IC1.L17, IC11.14
/BT_HCI_TX: IC11.7, R142.2
/BT_HCI_TX.SIP: IC1.L16, IC11.20
/CEC: D1.C, IC9.30, X5.15
/CLKOUT2: FB7.1, IC11.16, P2.18, P9.41, R14.1
/DVI_5V: F1.1, R115.1, R118.1, X5.19
/EHRPWM1A: IC1.U14, P9.14
/EHRPWM1B: IC1.T14, P9.16
/EHRPWM2A: IC1.U10, P8.19
/EHRPWM2B: IC1.T10, P8.13
/EMMC_RSTN: IC22.K5, R29.1, R33.1
/EXT_SWING: IC9.34, R119.1
/GPIO0_7: P9.42, R36.1, R38.1
/GPIO0_26: IC1.T11, P8.14
/GPIO0_27: IC1.U12, P8.17
/GPIO1_12: IC1.T12, P8.12
/GPIO1_13: IC1.R12, P8.11
/GPIO1_14: IC1.V13, P8.16
/GPIO1_15: IC1.U13, P8.15
/GPIO1_16: P9.15, R54.1
/GPIO1_16.SIP: IC1.R13, R54.2
/GPIO1_17: IC1.V14, P9.23
/GPIO1_28: IC1.U18, P9.12
/GPIO1_29: IC1.V6, P8.26
/GPIO2_1: IC1.V12, P8.18
/GPIO3_19: IC1.C13, P9.27
/GPIO3_21: IC1.A14, P9.25, R110.2
/HDMICLK_DIS#: IC1.V17, OSC1.1
/HDMI_INT: IC1.U16, IC9.50, R121.2
/HPD: IC9.31, X5.1
/I2C0_SCL: IC1.C16, IC1.C20, IC4.1, IC9.52, R41.2
/I2C0_SDA: IC1.C17, IC1.C19, IC4.3, IC9.51, R42.2
/I2C1_SCL: IC1.A16, P9.17
/I2C1_SDA: IC1.B16, P9.18
/I2C2_SCL: IC1.D17, P9.19
/I2C2_SDA: IC1.D18, P9.20
/JTAG_EMU0: IC1.C14, P2.13, R43.2
/JTAG_EMU1: IC1.B14, P2.14, R53.2
/JTAG_TCK: IC1.A12, P2.9, P2.11
/JTAG_TDI: IC1.B11, P2.3
/JTAG_TDO: IC1.A11, P2.7
/JTAG_TMS: IC1.C11, P2.1
/JTAG_TRSTN: IC1.B10, P2.2, R52.1
/LCD.CLOCK: IC9.4, P8.28, R34.1
/LCD.D0.B0--B3: C42.1, IC1.R1, IC9.15, P8.45, R87.2
/LCD.D1.B1--B4: C41.1, IC1.R2, IC9.13, P8.46, R85.2
/LCD.D2.B2--B5: C40.1, IC1.R3, IC9.12, P8.43, R82.1, R88.1
/LCD.D3.B3--B6: C39.1, IC1.R4, IC9.11, P8.44, R80.1
/LCD.D4.B4--B7: C38.1, IC1.T1, IC9.10, P8.41, R78.1
/LCD.D5.G0--G2: C37.1, IC1.T2, IC9.7, P8.42, R76.1
/LCD.D6.G1--G3: C36.1, IC1.T3, IC9.6, P8.39, R75.2
/LCD.D7.G2--G4: C35.1, IC1.T4, IC9.3, P8.40, R73.2
/LCD.D8.G3--G5: C34.1, IC1.U1, IC9.2, P8.37, R71.2
/LCD.D9.G4--G6: C33.1, IC1.U2, IC9.1, P8.38, R69.2
/LCD.D10.G5--G7: C32.1, IC1.U3, IC9.64, P8.36, R67.2
/LCD.D11.R0--R3: C31.1, IC1.U4, IC9.60, P8.34, R65.2
/LCD.D12.R1--R4: C30.1, IC1.V2, IC9.59, P8.35, R63.2
/LCD.D13.R2--R5: C29.1, IC1.V3, IC9.58, P8.33, R61.2
/LCD.D14.R3--R6: C28.1, IC1.V4, IC9.57, P8.31, R58.1
/LCD.D15.R4--R7: C27.1, IC1.T5, IC9.56, P8.32, R57.2
/LCD.ENABLE: IC9.20, P8.30, R39.1
/LCD.HSYNC: IC9.22, P8.29, R37.1
/LCD.VSYNC: IC9.21, P8.27, R35.1
/LDO_PGOOD: IC1.B5, IC1.B20
/LS_BUF_OE: IC1.L18, R131.2
/MCU.LCD.CLK: IC1.V5, R34.2
/MCU.LCD.EN: IC1.R6, R39.2
/MCU.LCD.HS: IC1.R5, R37.2
/MCU.LCD.VS: IC1.U5, R35.2
/MMC1_CLK: IC1.U9, IC22.M6, P8.21, R31.1
/MMC1_CMD: IC1.V9, IC22.M5, P8.20, R30.1
/MMC1_DAT0: IC1.U7, IC22.A3, P8.25, R12.1
/MMC1_DAT1: IC1.V7, IC22.A4, P8.24, R13.1
/MMC1_DAT2: IC1.R8, IC22.A5, P8.5, R16.1
/MMC1_DAT3: IC1.T8, IC22.B2, P8.6, R18.1
/MMC1_DAT4: IC1.U8, IC22.B3, P8.23, R20.1
/MMC1_DAT5: IC1.V8, IC22.B4, P8.22, R23.1
/MMC1_DAT6: IC1.R9, IC22.B5, P8.3, R25.1
/MMC1_DAT7: IC1.T9, IC22.B6, P8.4, R28.1
/PMIC_INT: IC1.B18, IC1.B19
/PMIC_NWAKEUP: IC1.A19, IC1.C5
/PMIC_PGOOD: IC1.A20, IC1.B15, IC2.2
/PWR_BUT: IC1.D20, P9.9, POWER1.3, POWER1.4
/RX<-TX: IC17.3, X1.5
/SD.CD: IC1.C15, P2.19, R7.1, X2.CD
/SD.CLK: IC1.G17, R3.1, X2.5
/SD.CMD: IC1.G18, R4.1, X2.3
/SD.D0: IC1.G16, R2.1, X2.7
/SD.D1: IC1.G15, R1.1, X2.8
/SD.D2: IC1.F18, R6.1, X2.1
/SD.D3: IC1.F17, R5.1, X2.2
/SELECT_5V: D2.K, D3.K, D4.K, FB1.1, R97.1, TP23.TP
/SLOW_CLK: IC11.5, R91.1
/SPI1_CS0: IC1.C12, IC9.25, P9.28
/SPI1_D0: IC1.B13, IC9.24, P9.29
/SPI1_D1: IC1.D12, P9.30
/SPI1_SCLK: IC1.A13, IC9.23, P9.31
/SYS_RESET#: C16.1, C21.1, IC1.A10, IC2.4, P2.15, P9.10, R32.2, RESET1.3, RESET1.4
/TEST: IC9.49, R114.2
/TIMER4: IC1.R7, P8.7
/TIMER5: IC1.T6, P8.9
/TIMER6: IC1.U6, P8.10
/TIMER7: IC1.T7, P8.8
/TX0+: IC8.5, IC9.40, X5.9
/TX0-: IC8.4, IC9.39, X5.11
/TX1+: IC7.2, IC9.43, X5.6
/TX1-: IC7.1, IC9.42, X5.8
/TX2+: IC7.5, IC9.45, X5.3
/TX2-: IC7.4, IC9.44, X5.5
/TX->RX: IC17.2, R123.1, X1.4
/TXC+: IC8.2, IC9.38, X5.12
/TXC-: IC8.1, IC9.37, X5.14
/UART0_RST#: IC1.E17, TP6.TP
/UART0_RXD: IC1.E15, IC17.6
/UART0_TXD: IC1.E16, IC17.5
/UART1_RXD: IC1.D16, P9.26
/UART1_TXD: IC1.D15, P9.24
/UART2_RXD: IC1.A17, P9.22
/UART2_TXD: IC1.B17, P9.21
/UART4_RXD: IC1.T17, P9.11
/UART4_TXD: IC1.U17, P9.13
/USB1_DRVVBUS: IC1.F15, IC12.4, R19.1
/USB1_OC#: IC1.T16, IC12.5, R122.2
/USB1_VBUS: FB4.2, IC1.T18
/USB.CLIENT.D+: IC1.N17, IC14.1, X4.D+
/USB.CLIENT.D-: IC1.N18, IC14.2, X4.D-
/USB.CLIENT.ID: IC1.P16, IC14.3, X4.ID
/USB.HOST.D+: IC1.R17, IC15.1, X3.3
/USB.HOST.D-: IC1.R18, IC15.2, X3.2
/USR0: IC1.V15, R104.2
/USR1: IC1.U15, R100.2
/USR2: IC1.T15, R96.2
/USR3: IC1.V16, R92.2
/VIN_BAT: IC1.Y2, IC1.Y3, TP2.P$1
/WL_EN: IC11.3, MOD1.40, R10.1, T3.G
/WL_EN.SIP: IC1.K18, R136.1
/WL_IRQ: IC11.9, R60.2
/WL_IRQ.SIP: IC1.H18, R134.1
/WL_SDIO_CLK: IC10.6, R64.2, R103.2
/WL_SDIO_CLK.SIP: IC1.L15, R126.1
/WL_SDIO_CMD: IC10.7, R62.2, R105.2
/WL_SDIO_CMD.SIP: IC1.J16, R86.1
/WL_SDIO_D0: IC10.1, R66.2, R98.2
/WL_SDIO_D0.SIP: IC1.J17, R130.1
/WL_SDIO_D1: IC10.3, R68.2, R99.2
/WL_SDIO_D1.SIP: IC1.J18, R129.1
/WL_SDIO_D2: IC10.4, R70.2, R101.2
/WL_SDIO_D2.SIP: IC1.K15, R128.1
/WL_SDIO_D3: IC10.5, R72.2, R102.2
/WL_SDIO_D3.SIP: IC1.H16, R127.1
/XDMA_EVENT_INTRO: FB5.2, IC13.1, P2.17
unnamed: ANT1.SIG, C46.1
unnamed: ANT2.SIG, C60.1
unnamed: BT1.A, R124.1
unnamed: BT1.K, T4.D
unnamed: C3.1, IC1.M20, Q4.2, R8.2
unnamed: C3.2, C4.2, IC1.L20
unnamed: C4.1, IC1.K20, Q4.1, R8.1
unnamed: C5.1, IC1.H20, Q2.P$1, R56.2
unnamed: C5.2, C6.2, IC1.G20
unnamed: C6.1, IC1.F20, Q2.P$2, R56.1
unnamed: C46.2, MOD1.32
unnamed: C58.1, FB3.1, FB4.1, IC12.6, IC12.7, IC12.8, IC15.6
unnamed: C60.2, MOD1.18
unnamed: C7.1, C69.1, IC22.C2
unnamed: D1.A, R120.2
unnamed: FB3.2, X3.1
unnamed: FB5.1, IC1.A15
unnamed: FB6.1, IC13.5
unnamed: FB7.2, IC1.D14
unnamed: IC1.B4, R24.2
unnamed: IC1.B12, R38.2
unnamed: IC1.C6, IC1.D19
unnamed: IC1.C9, R21.2, R22.1
unnamed: IC1.C18, R36.2
unnamed: IC1.D13, R14.2
unnamed: IC1.P15, R26.1
unnamed: IC1.P17, R27.1
unnamed: IC1.R14, IC3.2
unnamed: IC3.4, R29.2
unnamed: IC4.5, R40.2, TP1.P$1
unnamed: IC5.1, R45.2, R46.2, R47.1
unnamed: IC5.2, R44.2, R45.1, T1.B
unnamed: IC6.1, R49.2, R50.2, R51.1
unnamed: IC6.2, R48.2, R49.1, T2.B
unnamed: IC9.32, R118.2, X5.18
unnamed: IC9.33, R115.2, X5.17
unnamed: IC10.10, IC11.10, R106.1, R131.1
unnamed: IC10.14, R86.2
unnamed: IC10.15, R126.2
unnamed: IC10.16, R127.2
unnamed: IC10.17, R128.2
unnamed: IC10.18, R129.2
unnamed: IC10.20, R130.2
unnamed: IC11.12, R134.2
unnamed: IC11.17, R135.2
unnamed: IC11.18, R136.2
unnamed: IC18.1, R89.2, R97.2
unnamed: IC18.5, R93.2, R94.1
unnamed: MOD1.6, R62.1
unnamed: MOD1.8, R64.1
unnamed: MOD1.10, R66.1
unnamed: MOD1.11, R68.1
unnamed: MOD1.12, R70.1
unnamed: MOD1.13, R72.1
unnamed: MOD1.14, R60.1, R111.2
unnamed: MOD1.26, TP12.TP
unnamed: MOD1.27, TP13.TP
unnamed: MOD1.42, TP14.TP
unnamed: MOD1.43, TP15.TP
unnamed: MOD1.50, R140.1
unnamed: MOD1.51, R141.1
unnamed: MOD1.52, R142.1
unnamed: MOD1.53, R143.1
unnamed: MOD1.56, TP16.TP
unnamed: MOD1.57, TP17.TP
unnamed: MOD1.58, TP18.TP
unnamed: MOD1.60, TP19.TP
unnamed: OSC1.3, R110.1
unnamed: OSC2.1, R90.2
unnamed: PWR1.K, R55.2
unnamed: R88.2, S2.1, S2.2
unnamed: R92.1, USR3.A
unnamed: R96.1, USR2.A
unnamed: R100.1, USR1.A
unnamed: R104.1, USR0.A
unnamed: R125.1, WL1.A
unnamed: T3.D, WL1.K

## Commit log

2019-11-18 create shared objs test
2019-11-18 move .py files into lib
2019-11-18 readme and License
2019-11-18 dockerfile
2019-12-11 checkout submodule master branches
2019-12-11 branch version submodule update
2019-12-11 update branches again
2019-12-12 need to incl. shared objs script in cmake
2019-12-16 build sh script
2019-12-18 change to whatever swig is in path
2019-12-18 convert to python 3
2019-12-18 point modules to masters
2019-12-18 testflow
2019-12-18 demo
2019-12-19 add tests directory
2019-12-23 new placer branch
2020-01-01 update branch versions
2020-01-01 clean.sh
2020-01-01 testcases update
2020-01-04 add postprocessing for pad layer propagation
2020-01-04 typo in prop script tree traversal
2020-01-04 corrected leaf matching in check script
2020-01-08 modules
2020-01-08 module update
2020-01-09 removed clone line
2020-01-09 removed cds
2020-01-09 command line app for running layout
2020-01-09 added skip_placement option
2020-04-15 update versions
2020-05-12 adding a Jenkinsfile
2020-05-14 removed sudos
2020-05-14 Update Jenkinsfile
2020-05-14 updating placer
2020-05-14 initial jenkins scripts
2020-05-14 add scripts to jenkins file
2020-05-14 jenkins scripts executable
2020-05-14 dummy commit to trigger jenkins
2020-05-14 line ending problem
2020-05-14 add ubuntu install script to jenkins install
2020-05-14 fixed some paths
2020-05-14 added a test
2020-05-14 test runs placement
2020-05-14 set -e for test failure
2020-05-15 added a non-root user to the docker image
2020-05-20 docker build update for jenkins
2020-05-25 added router initialization call
2020-05-25 removed grid scale option, it was causeing the routing scale to be incorrect
2020-05-27 script to run all benchmarks
2020-05-27 proper router initialization and better defulat params
2020-05-27 corrected paths
2020-05-28 metric checking and timing
2020-06-02 starting documentation
2020-06-02 skeleton for database and placer
2020-06-02 skeleton for router; namespaces
2020-06-02 typo
2020-06-02 update placer
2020-06-03 quickstart and other doc fixes
2020-06-17 more scripts
